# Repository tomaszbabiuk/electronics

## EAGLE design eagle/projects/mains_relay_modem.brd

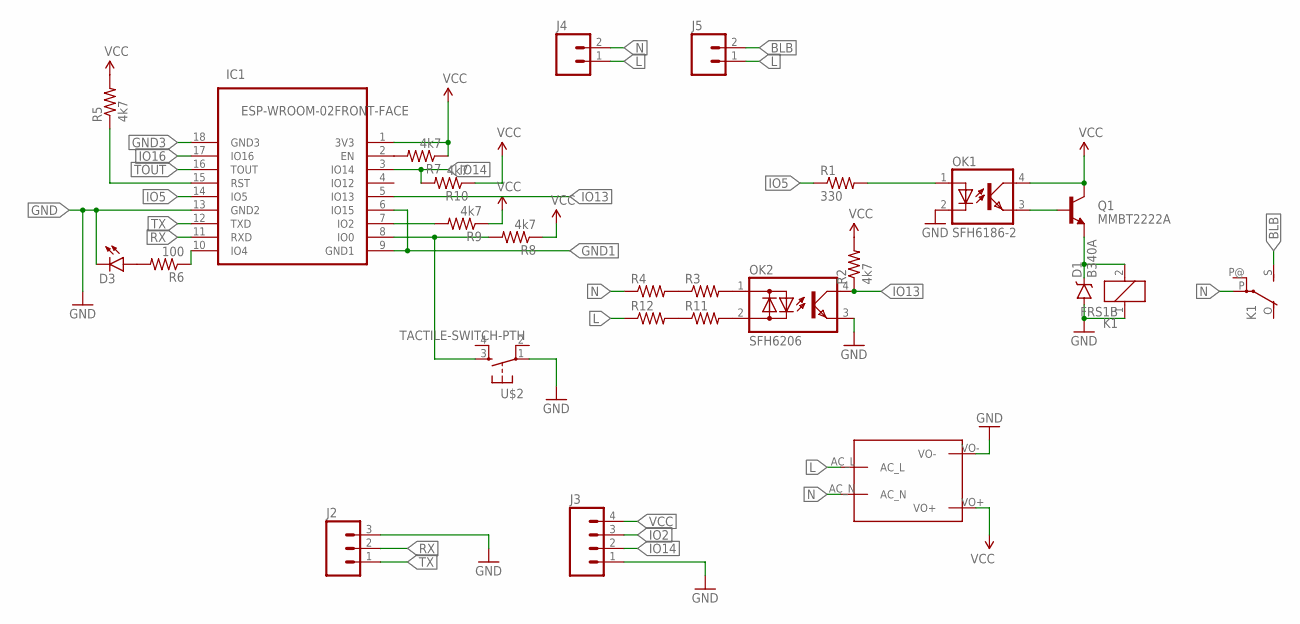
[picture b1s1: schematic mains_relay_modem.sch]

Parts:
D1: B340A; SMA-DIODE
D3: LED3MM
IC1: ESP-WROOM-02FRONT-FACE; FRONT-FACE
J2: M03PTH; 1X03
J3: M04NO_SILK_ALL_ROUND; 1X04_NO_SILK_ALL_ROUND
J4, J5: M025MM; SCREWTERMINAL-5MM-2
K1: FRS1B
OK1: SFH6186-2; SMD4
OK2: SFH6206; DIL4-SMD
Q1: MMBT2222A; SOT23-3
R1: 330; 0805
R2, R5, R7, R8, R9, R10: 4k7; 0805
R3, R4, R11, R12: RESISTOR0805-RES; 0805
R6: 100; 0805
U$1: MAINS_CONVERTERS; HLK-PM01
U$2: TACTILE-SWITCH-PTH; TAC-SWITCH-PTH

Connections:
BLB: J5.2, K1.S
GND: D1.A, D3.K (C), IC1.13 (GND2), J2.3, J3.1, K1.1, OK1.2 (C), OK2.3 (E), U$1.VO-, U$2.1
GND1: IC1.6 (IO15), IC1.9 (GND1)
GND3: IC1.18 (GND3)
IO2: IC1.7 (IO2), J3.3, R9.2
IO5: IC1.14 (IO5), R1.1
IO13: IC1.5 (IO13), OK2.4 (C), R2.1
IO14: IC1.3 (IO14), J3.2, R10.2
IO16: IC1.17 (IO16)
L: J4.1, J5.1, R12.1, U$1.AC_L
N: J4.2, K1.P, R4.1, U$1.AC_N
unnamed: IC1.10 (IO4), R6.1
unnamed: D3.A, R6.2
unnamed: IC1.2 (EN), R7.2
unnamed: D1.C, K1.2, Q1.2 (E)
unnamed: OK2.1 (AC1), R3.2
unnamed: R3.1, R4.2
unnamed: OK1.1 (A), R1.2
unnamed: OK1.3 (EMIT), Q1.1 (B)
unnamed: OK2.2 (AC2), R11.2
unnamed: IC1.15 (RST), R5.1
unnamed: IC1.8 (IO0), R8.2, U$2.3
unnamed: R11.1, R12.2
RX: IC1.11 (RXD), J2.2
TOUT: IC1.16 (TOUT)
TX: IC1.12 (TXD), J2.1
VCC: IC1.1 (3V3), J3.4, OK1.4 (COL), Q1.3 (C), R2.2, R5.2, R7.1, R8.1, R9.1, R10.1, U$1.VO+

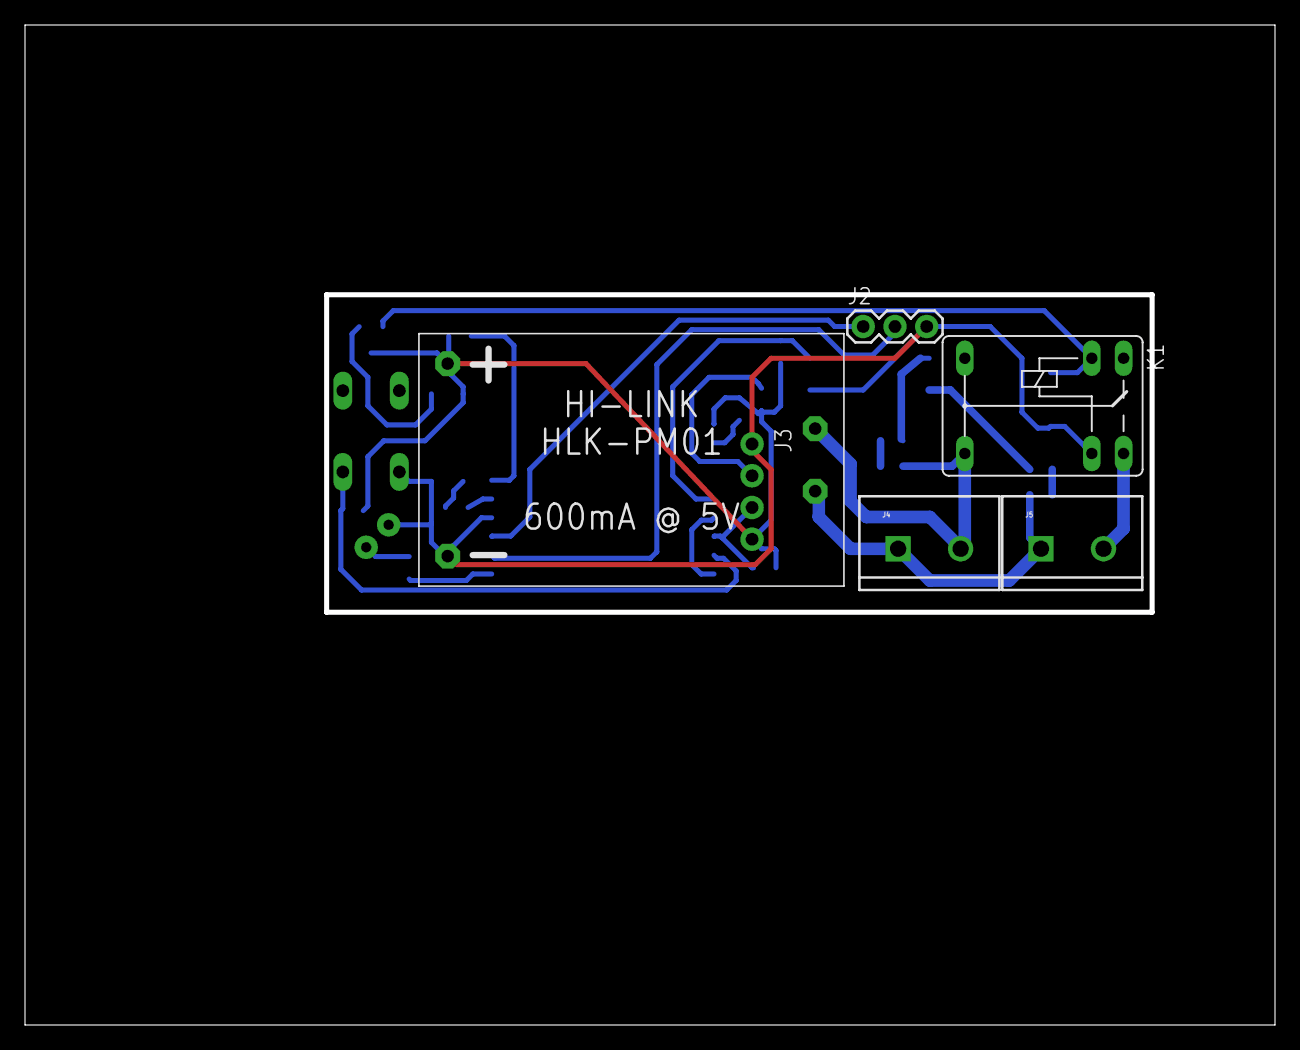
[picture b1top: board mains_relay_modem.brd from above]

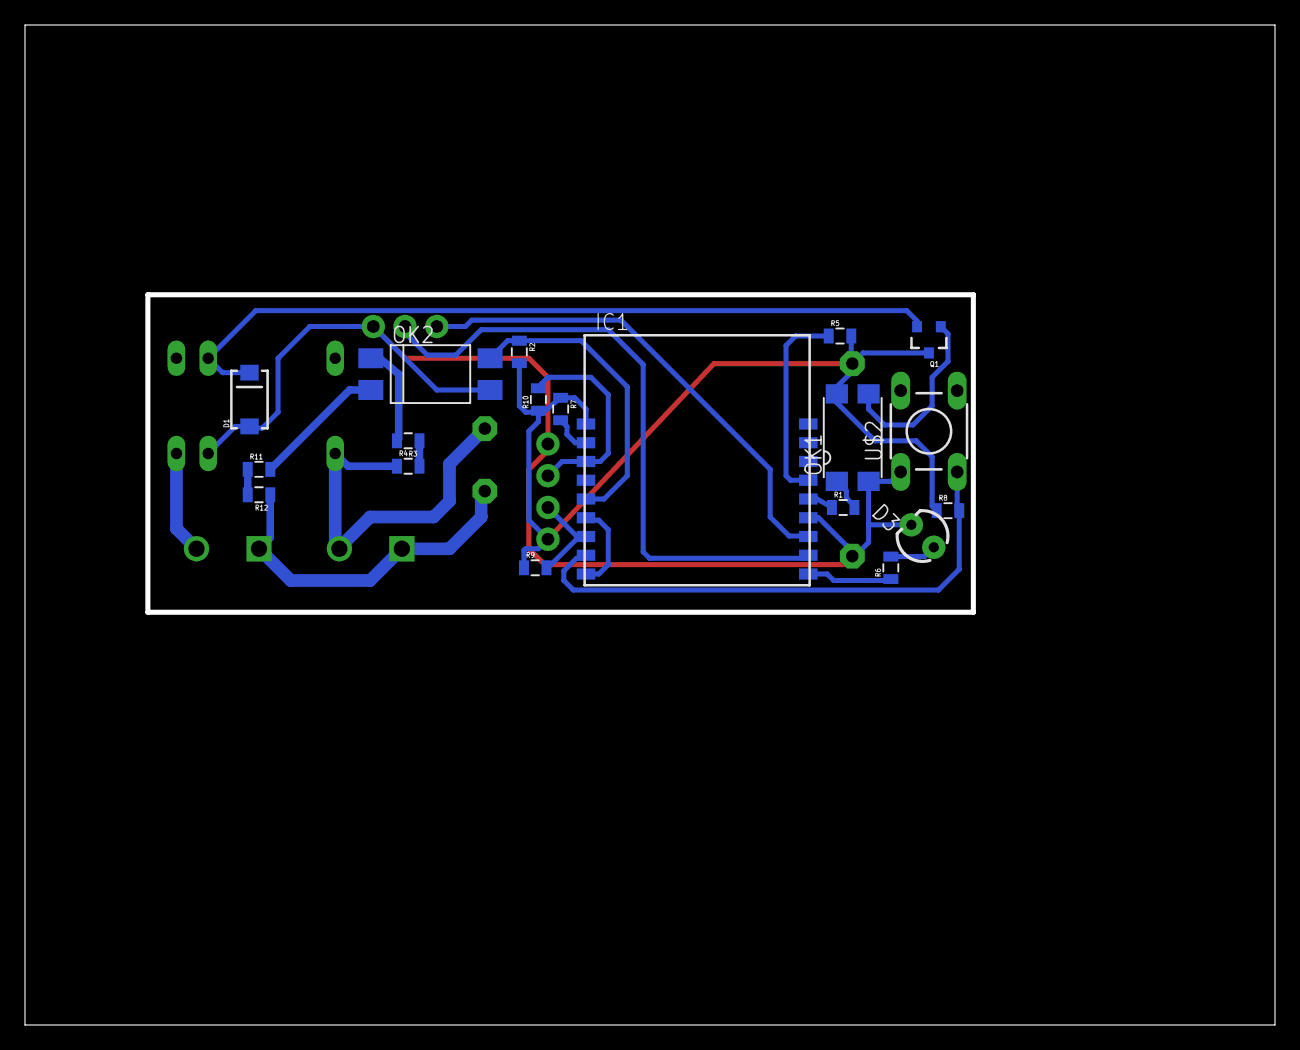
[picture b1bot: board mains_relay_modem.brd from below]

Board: 2 copper layers, 100.0 x 80.0 mm, 25 parts (19 on the bottom side), 24 nets.

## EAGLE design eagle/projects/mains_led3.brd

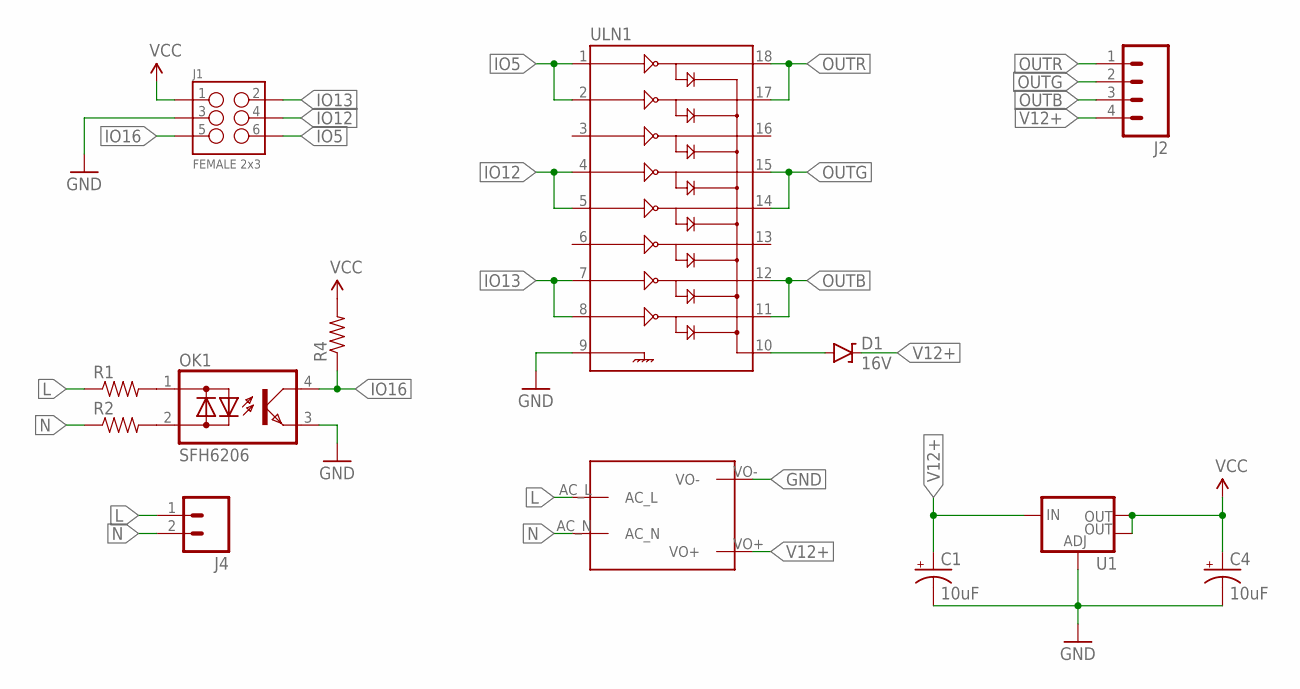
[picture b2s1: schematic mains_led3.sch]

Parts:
C1, C4: 10uF; EIA3216-KIT
D1: 16V; SOD-123
J1: FEMALE 2x3; 2X3-SHROUDED
J2: M04NO_SILK_ALL_ROUND; 1X04_NO_SILK_ALL_ROUND
J4: M023.5MM; SCREWTERMINAL-3.5MM-2
OK1: SFH6206; DIL4-SMD
R1, R2: RESISTORPTH-1/4W-VERT; AXIAL-0.1
R4: RESISTOR0805-RES; 0805
U1: V_REG_LM1117SOT223; SOT223
U$1: MAINS_CONVERTERS; HLK-PM01
ULN1: ULN2803SOICW; SO18L

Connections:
GND: C1.C (-), C4.C (-), J1.3, OK1.3 (E), U1.1 (ADJ), U$1.VO-, ULN1.9
IO5: J1.6, ULN1.1, ULN1.2
IO12: J1.4, ULN1.4, ULN1.5
IO13: J1.2, ULN1.7, ULN1.8
IO16: J1.5, OK1.4 (C), R4.1
L: J4.1, R1.P$1 (1), U$1.AC_L
N: J4.2, R2.P$1 (1), U$1.AC_N
unnamed: D1.A, ULN1.10
unnamed: OK1.1 (AC1), R1.P$2 (2)
unnamed: OK1.2 (AC2), R2.P$2 (2)
OUTB: J2.3, ULN1.11, ULN1.12
OUTG: J2.2, ULN1.14, ULN1.15
OUTR: J2.1, ULN1.17, ULN1.18
V12+: C1.A (+), D1.C, J2.4, U1.3 (IN), U$1.VO+
VCC: C4.A (+), J1.1, R4.2, U1.2 (OUT), U1.4 (OUT)

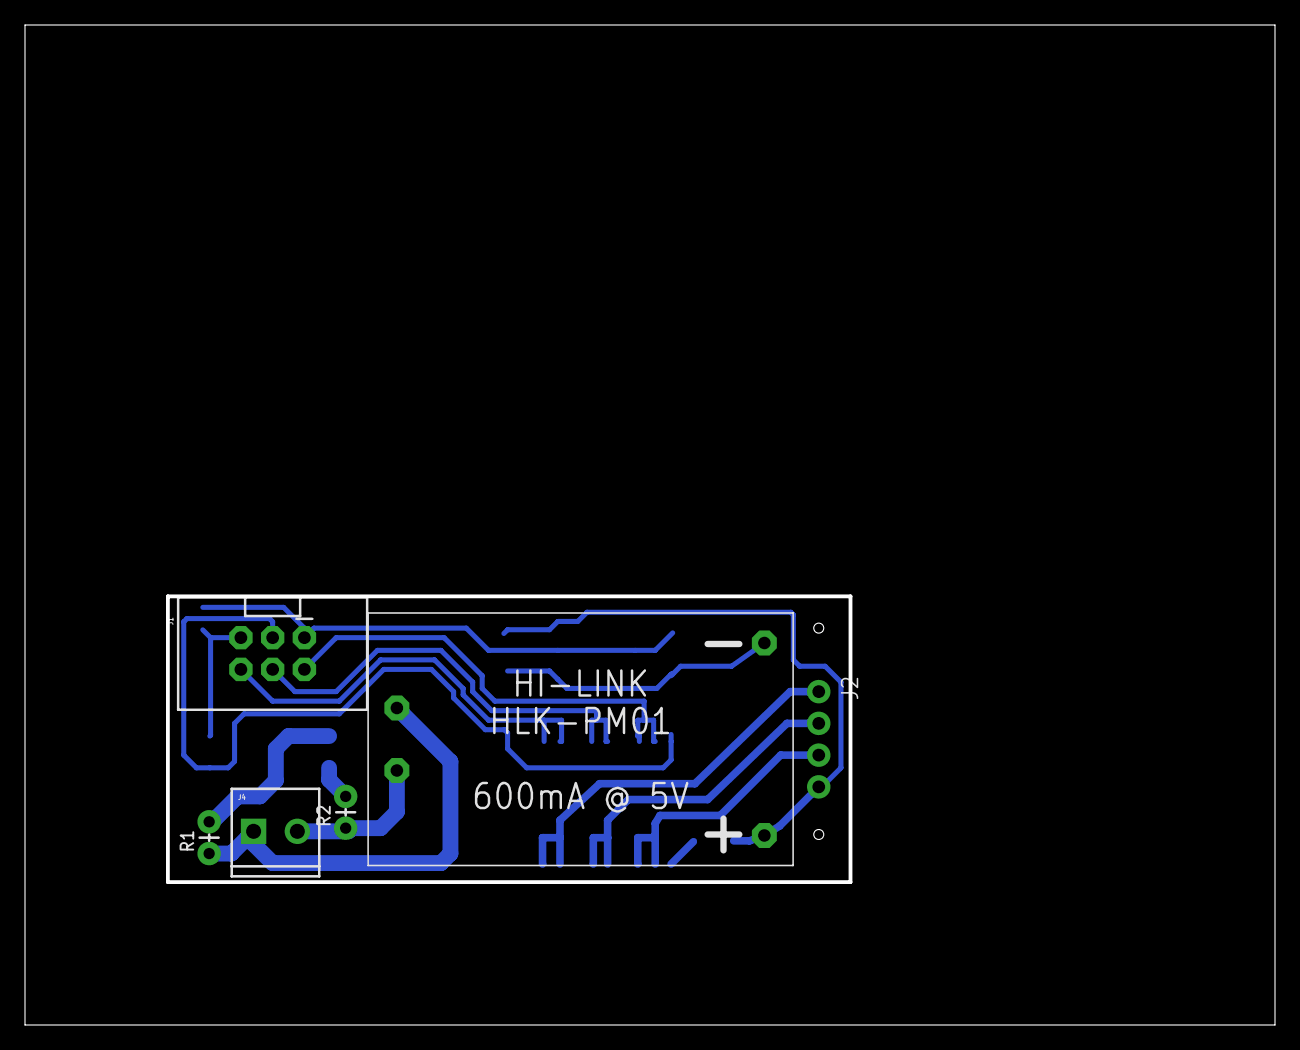
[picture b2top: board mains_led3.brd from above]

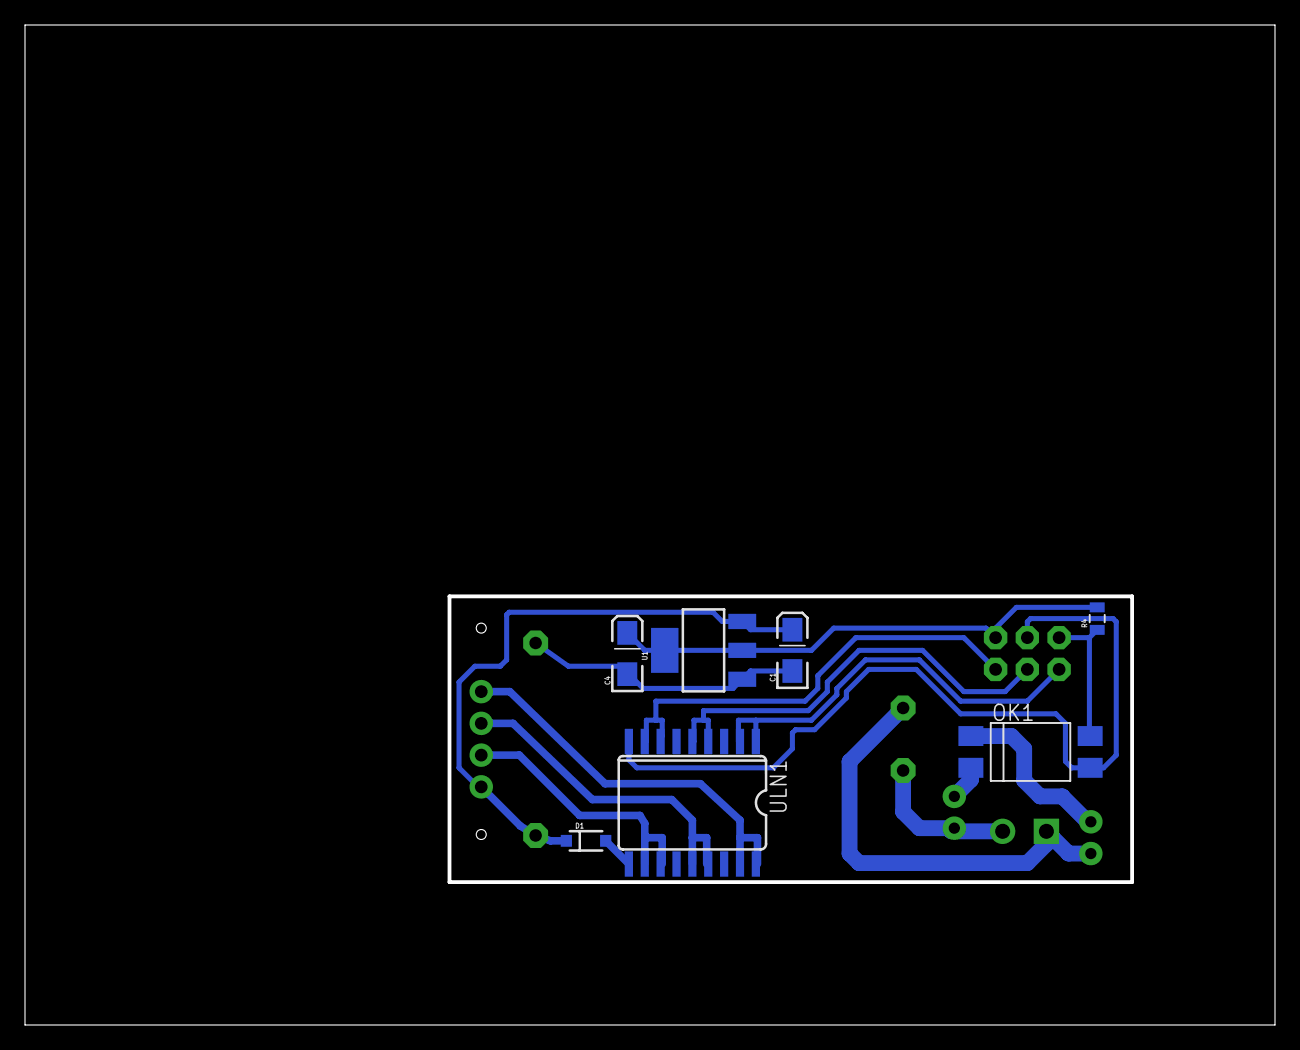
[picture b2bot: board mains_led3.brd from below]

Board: 2 copper layers, 100.0 x 80.0 mm, 13 parts (7 on the bottom side), 15 nets.

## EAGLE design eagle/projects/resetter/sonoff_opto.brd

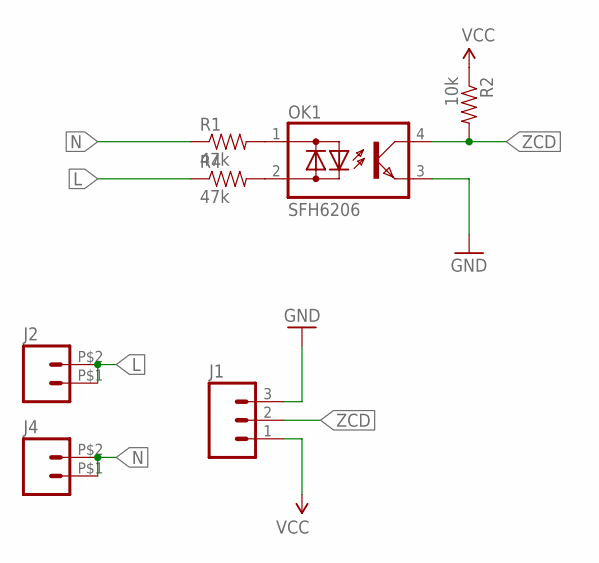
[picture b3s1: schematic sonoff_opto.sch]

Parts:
J1: M03PTH; 1X03
J2, J4: M02PTH2; 1X02_BIG
OK1: SFH6206; DIL4-SMD
R1, R4: 47k; AXIAL-0.4
R2: 10k; 0805

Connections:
GND: J1.3, OK1.3 (E)
L: J2.P$1 (1), J2.P$2 (2), R4.P$1 (1)
N: J4.P$1 (1), J4.P$2 (2), R1.P$1 (1)
unnamed: OK1.1 (AC1), R1.P$2 (2)
unnamed: OK1.2 (AC2), R4.P$2 (2)
VCC: J1.1, R2.1
ZCD: J1.2, OK1.4 (C), R2.2

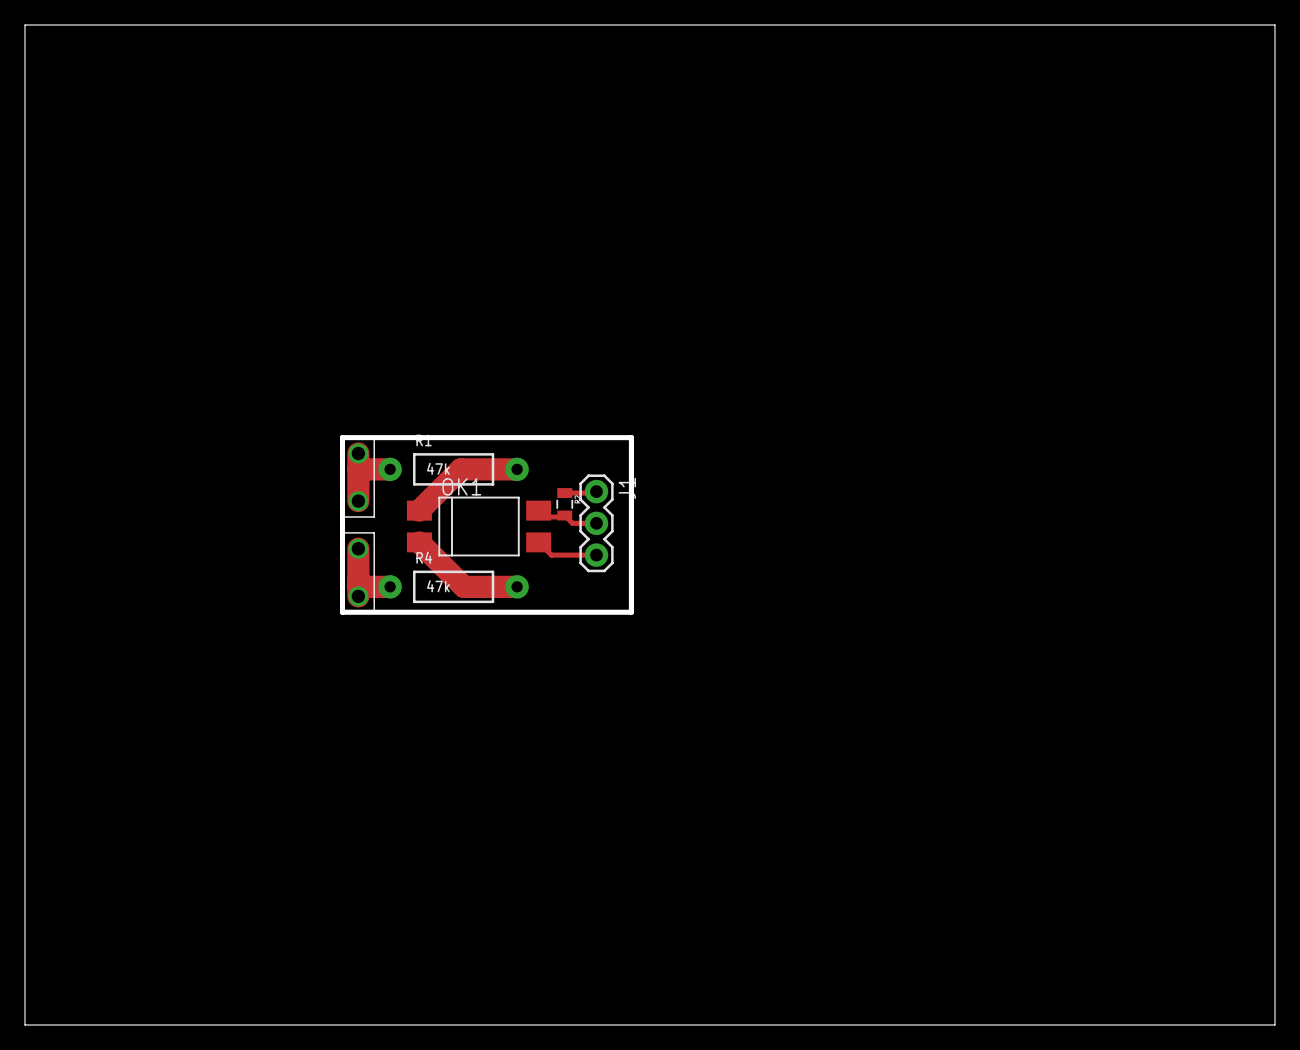
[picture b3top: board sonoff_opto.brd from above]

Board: 2 copper layers, 100.0 x 80.0 mm, 7 parts (0 on the bottom side), 7 nets.

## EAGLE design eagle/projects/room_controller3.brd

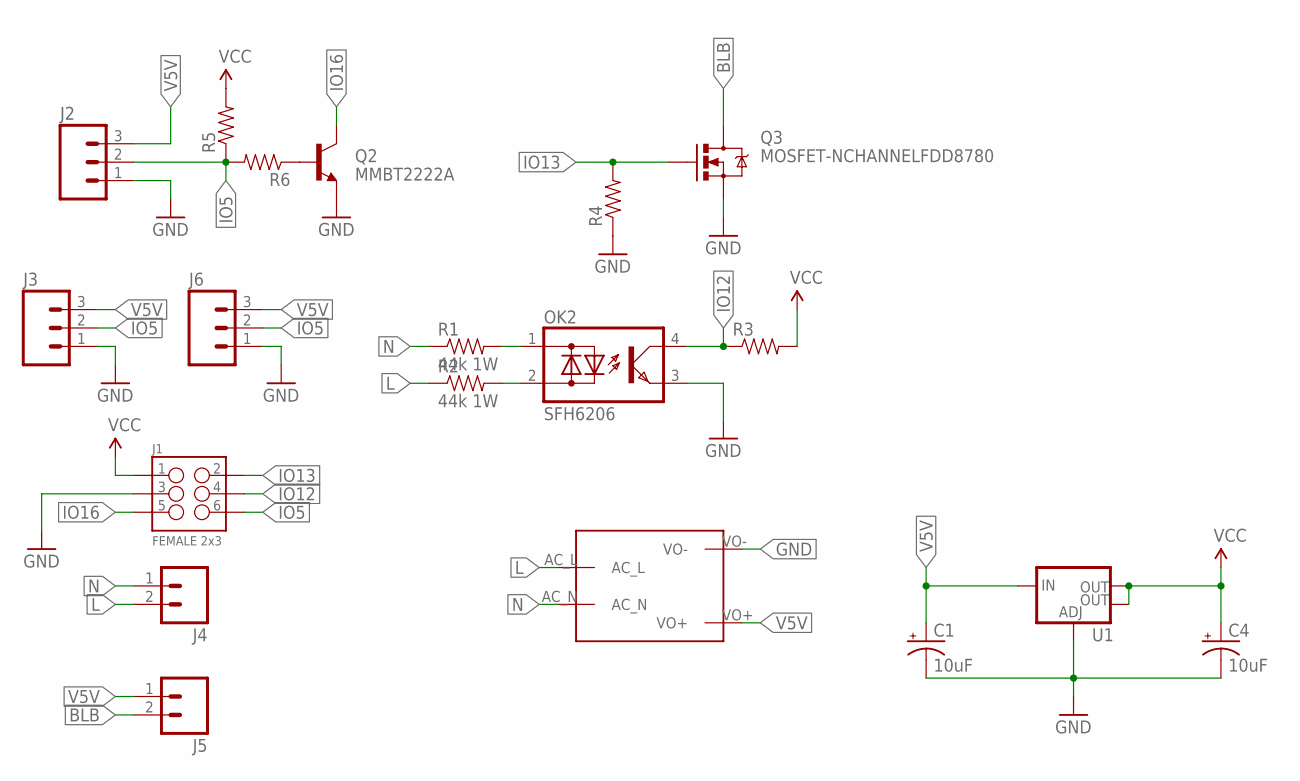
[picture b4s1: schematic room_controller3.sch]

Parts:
C1, C4: 10uF; EIA3216-KIT
J1: FEMALE 2x3; 2X3-SHROUDED
J2, J3, J6: M03PTH; 1X03
J4, J5: M025MM; SCREWTERMINAL-5MM-2
OK2: SFH6206; DIL4-SMD
Q2: MMBT2222A; SOT23-3
Q3: MOSFET-NCHANNELFDD8780; DPAK
R1, R2: 44k 1W; AXIAL-0.4
R3, R4, R5, R6: RESISTOR0805-RES; 0805
U1: V_REG_LM1117SOT223; SOT223
U$1: MAINS_CONVERTERS; HLK-PM01

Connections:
BLB: J5.2, Q3.4 (D)
GND: C1.C (-), C4.C (-), J1.3, J2.1, J3.1, J6.1, OK2.3 (E), Q2.2 (E), Q3.3 (S), R4.1, U1.1 (ADJ), U$1.VO-
IO5: J1.6, J2.2, J3.2, J6.2, R5.1, R6.2
IO12: J1.4, OK2.4 (C), R3.1
IO13: J1.2, Q3.1 (G), R4.2
IO16: J1.5, Q2.3 (C)
L: J4.2, R2.P$1 (1), U$1.AC_L
N: J4.1, R1.P$1 (1), U$1.AC_N
unnamed: OK2.1 (AC1), R1.P$2 (2)
unnamed: OK2.2 (AC2), R2.P$2 (2)
unnamed: Q2.1 (B), R6.1
V5V: C1.A (+), J2.3, J3.3, J5.1, J6.3, U1.3 (IN), U$1.VO+
VCC: C4.A (+), J1.1, R3.2, R5.2, U1.2 (OUT), U1.4 (OUT)

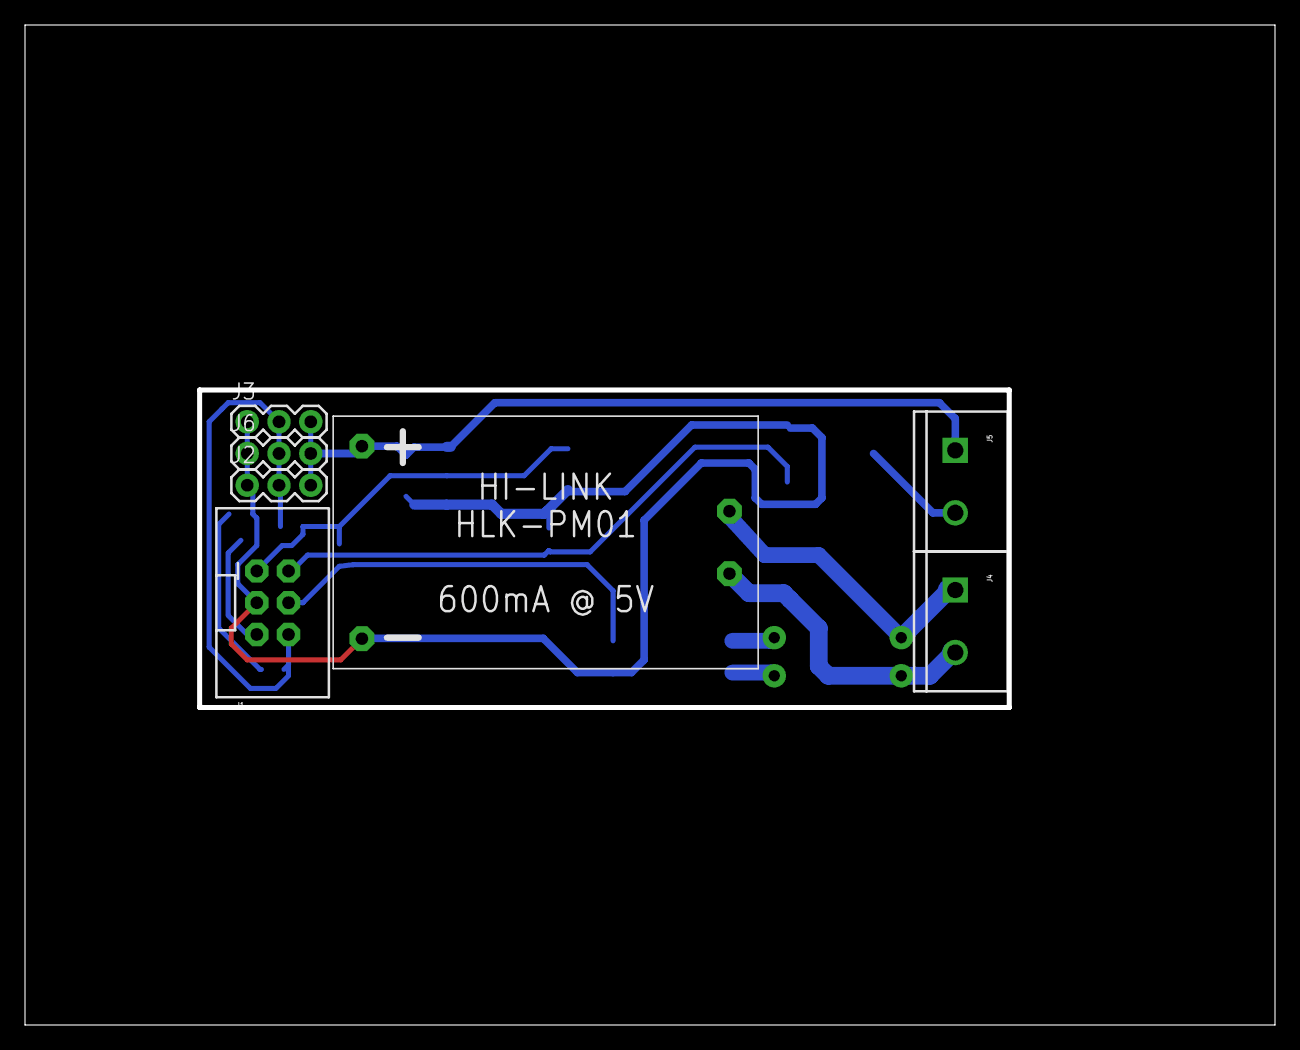
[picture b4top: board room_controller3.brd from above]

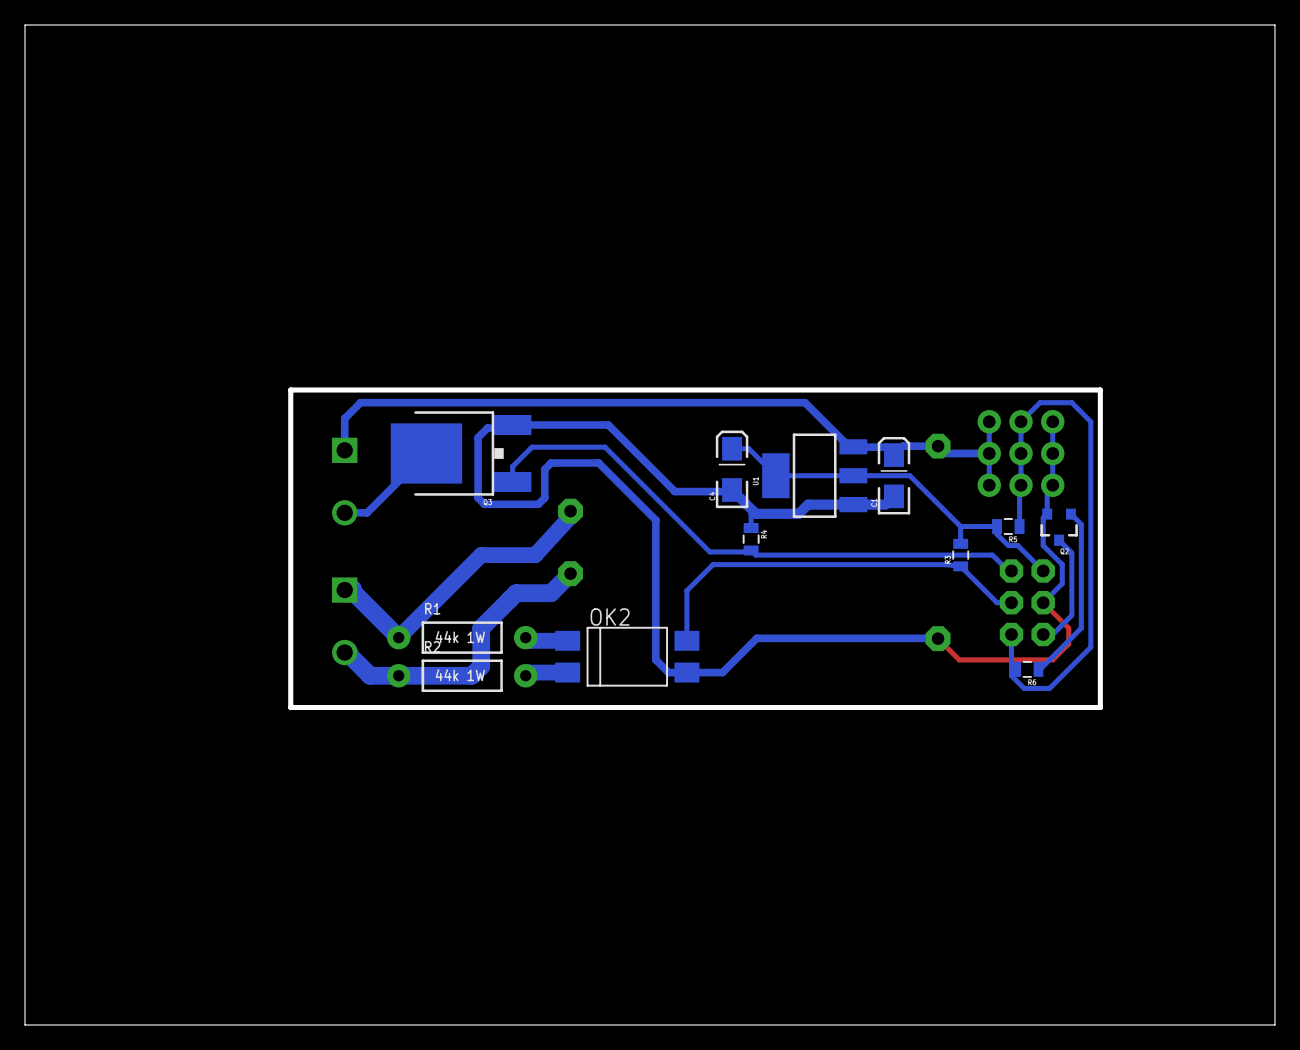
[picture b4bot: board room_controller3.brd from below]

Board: 2 copper layers, 100.0 x 80.0 mm, 19 parts (12 on the bottom side), 13 nets.

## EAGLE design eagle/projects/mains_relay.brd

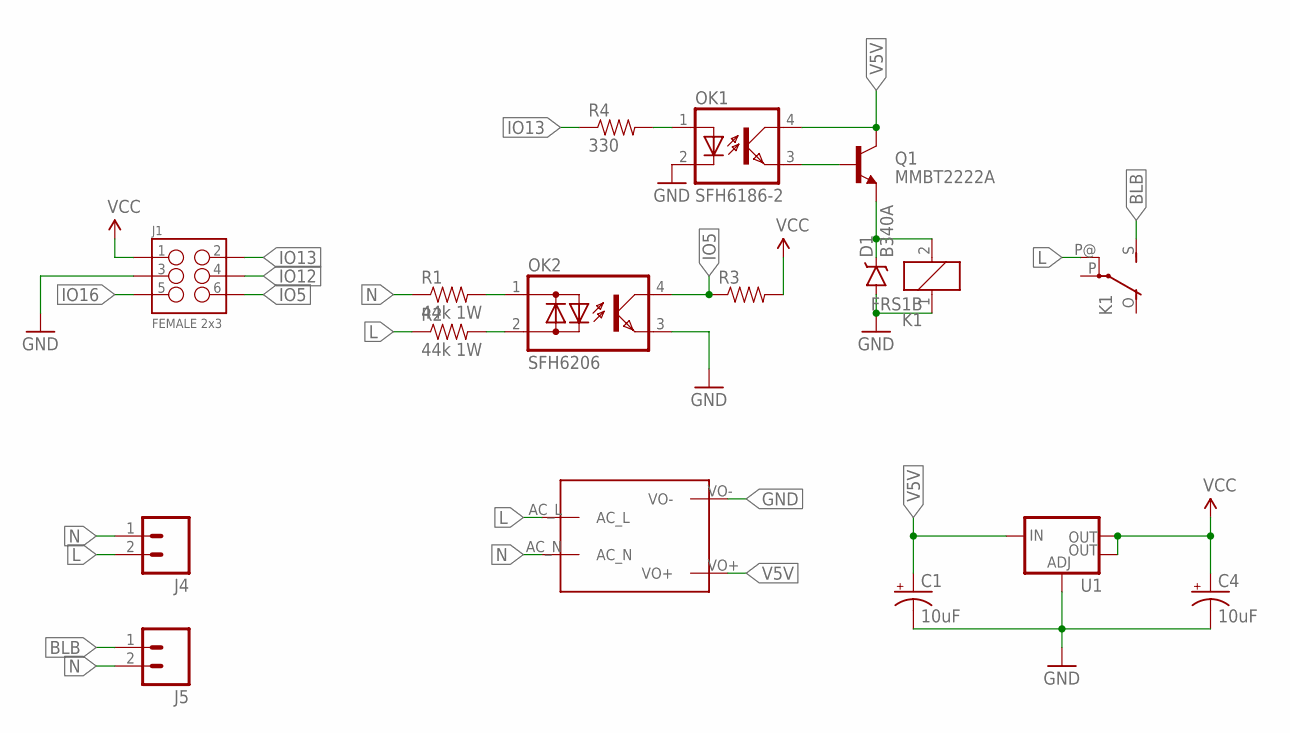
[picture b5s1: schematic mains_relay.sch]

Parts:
C1, C4: 10uF; EIA3216-KIT
D1: B340A; SMA-DIODE
J1: FEMALE 2x3; 2X3-SHROUDED
J4, J5: M025MM; SCREWTERMINAL-5MM-2
K1: FRS1B
OK1: SFH6186-2; SMD4
OK2: SFH6206; DIL4-SMD
Q1: MMBT2222A; SOT23-3
R1, R2: 44k 1W; AXIAL-0.4
R3: RESISTOR0805-RES; 0805
R4: 330; 0805
U1: V_REG_LM1117SOT223; SOT223
U$1: MAINS_CONVERTERS; HLK-PM01

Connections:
BLB: J5.1, K1.S
GND: C1.C (-), C4.C (-), D1.A, J1.3, K1.1, OK1.2 (C), OK2.3 (E), U1.1 (ADJ), U$1.VO-
IO5: J1.6, OK2.4 (C), R3.1
IO12: J1.4
IO13: J1.2, R4.1
IO16: J1.5
L: J4.2, K1.P@, R2.P$1 (1), U$1.AC_L
N: J4.1, J5.2, R1.P$1 (1), U$1.AC_N
unnamed: OK2.1 (AC1), R1.P$2 (2)
unnamed: OK2.2 (AC2), R2.P$2 (2)
unnamed: OK1.1 (A), R4.2
unnamed: D1.C, K1.2, Q1.2 (E)
unnamed: OK1.3 (EMIT), Q1.1 (B)
V5V: C1.A (+), OK1.4 (COL), Q1.3 (C), U1.3 (IN), U$1.VO+
VCC: C4.A (+), J1.1, R3.2, U1.2 (OUT), U1.4 (OUT)

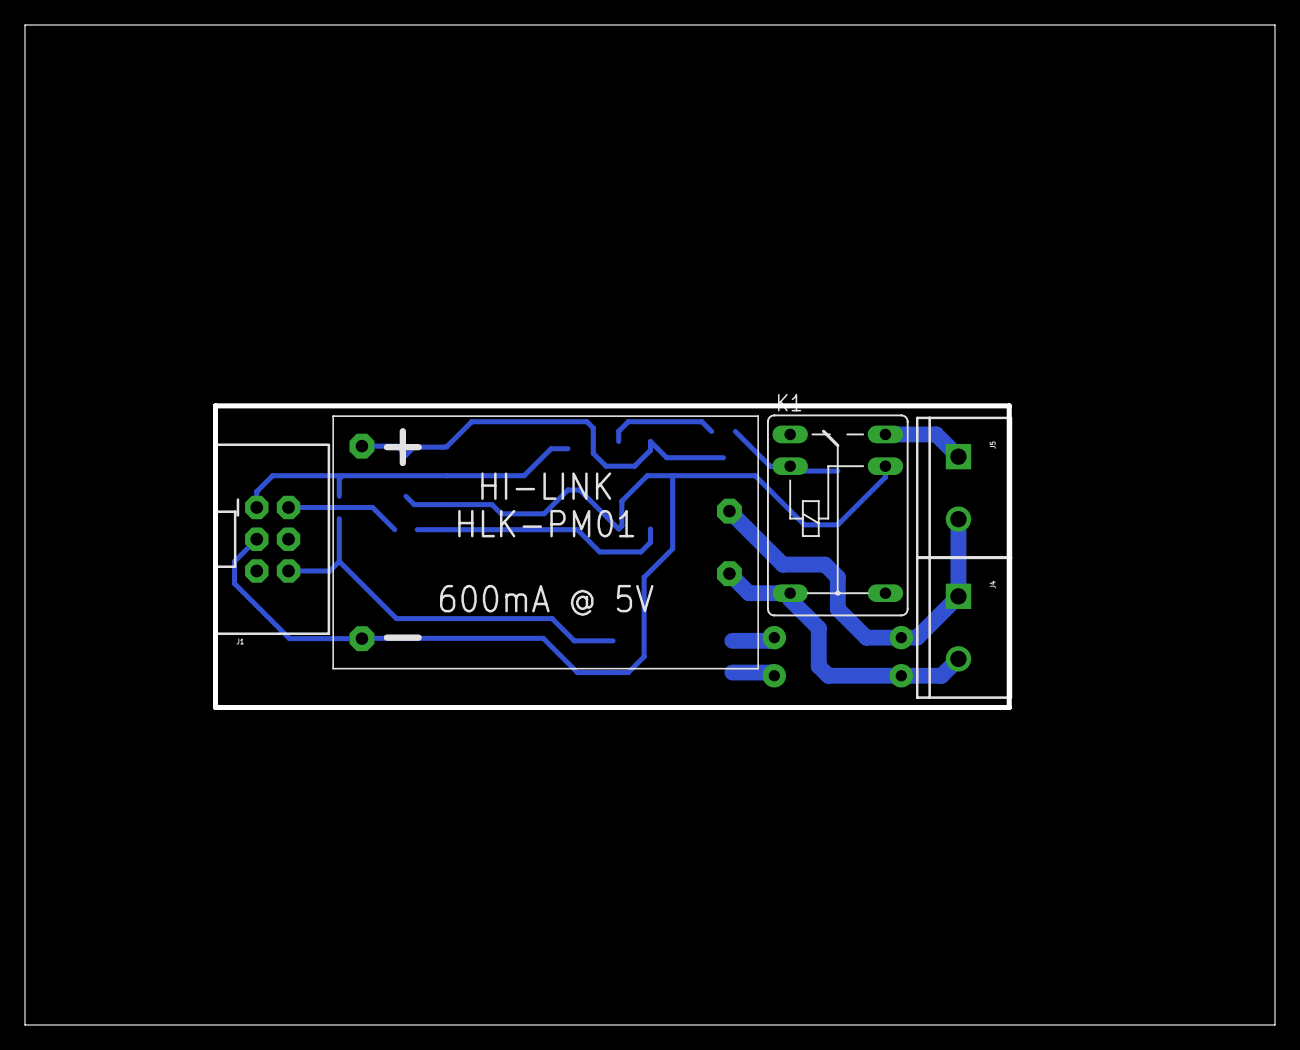
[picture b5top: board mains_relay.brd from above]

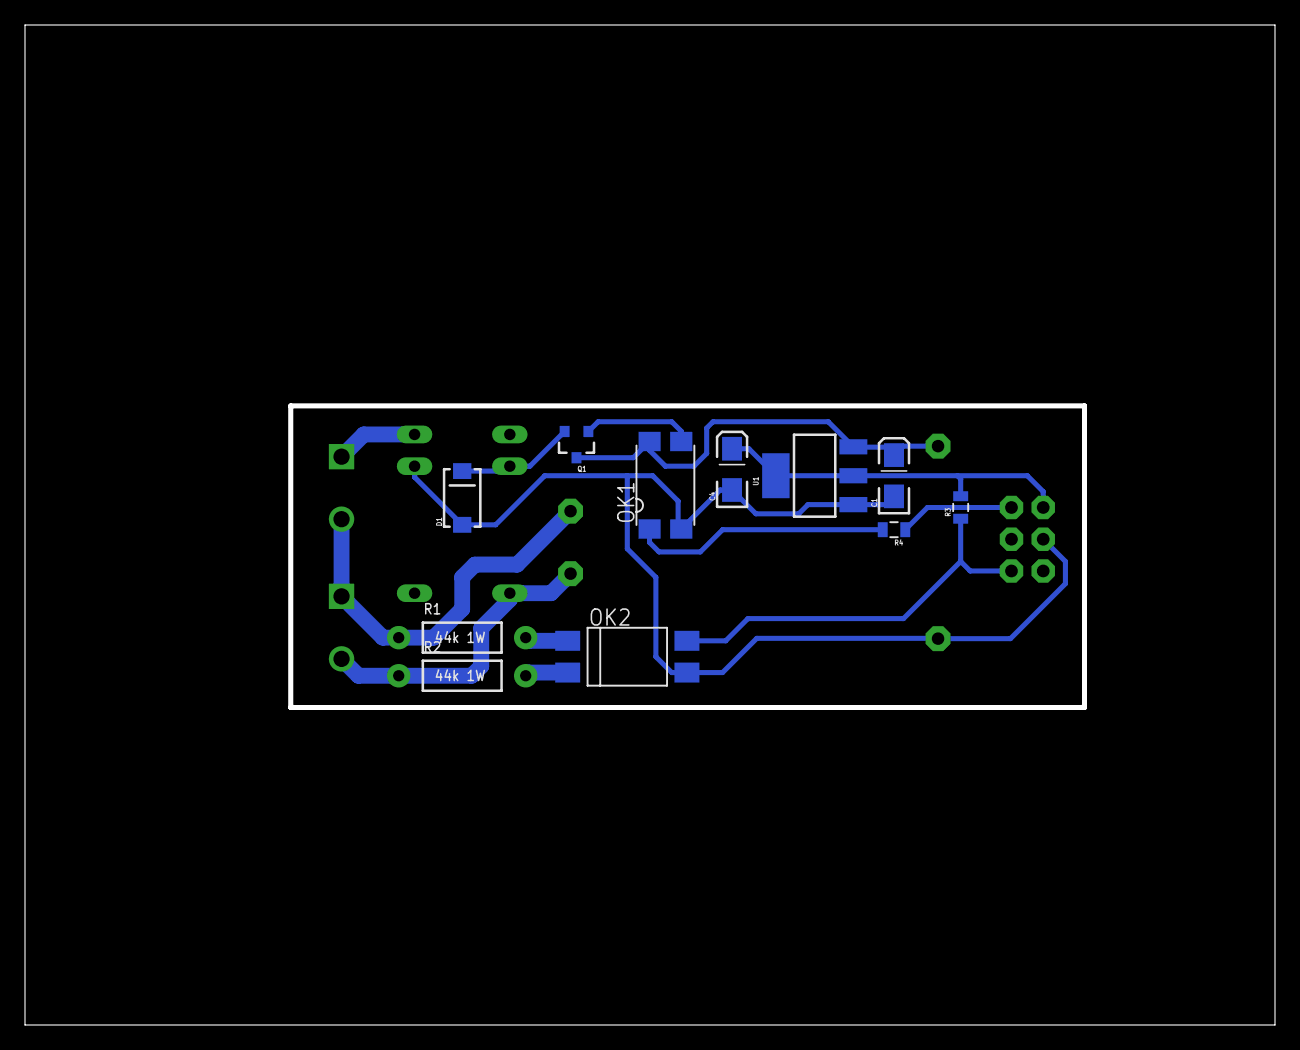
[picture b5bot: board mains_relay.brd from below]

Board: 2 copper layers, 100.0 x 80.0 mm, 16 parts (11 on the bottom side), 13 nets.

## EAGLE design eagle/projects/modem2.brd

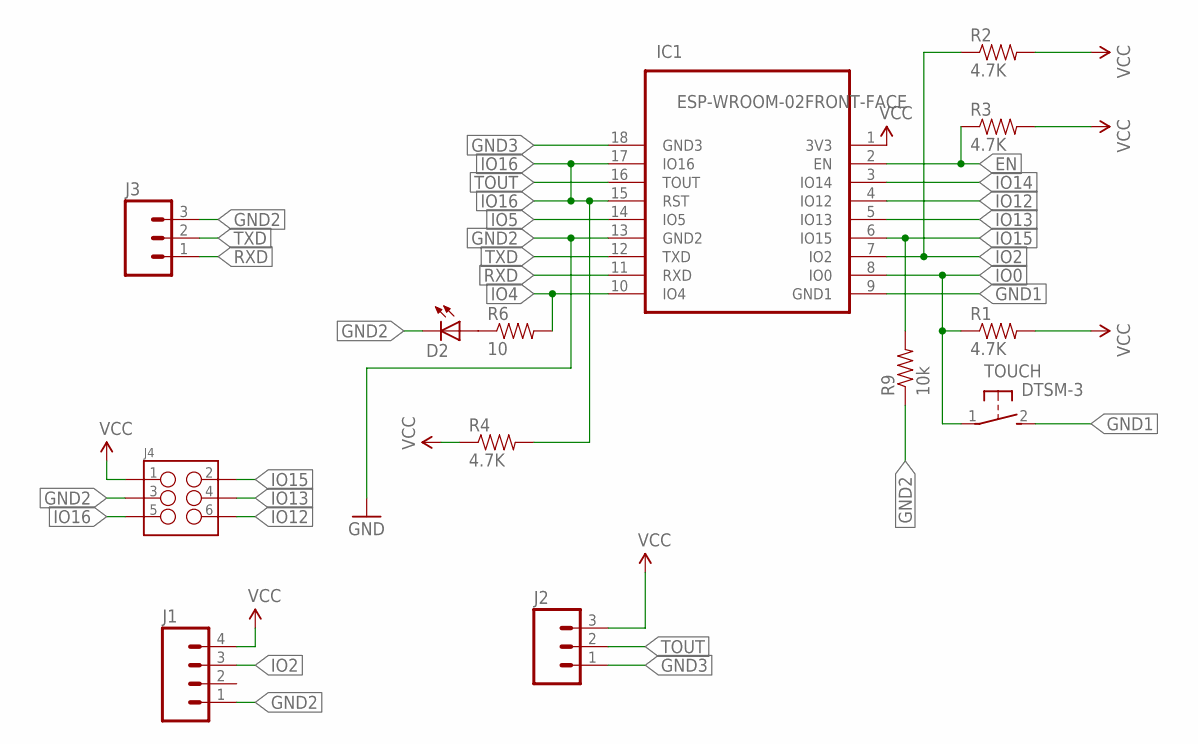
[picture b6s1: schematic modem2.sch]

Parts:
D2: LEDCHIPLED_0805; CHIPLED_0805
IC1: ESP-WROOM-02FRONT-FACE; FRONT-FACE
J1: M04NO_SILK_ALL_ROUND; 1X04_NO_SILK_ALL_ROUND
J2: M03PTH; 1X03
J3: M031X03_NO_SILK; 1X03_NO_SILK
J4: M03X2SHROUD; 2X3-SHROUDED
R1, R2, R3, R4: 4.7K; 0805
R6: 10; 0805
R9: 10k; 0805
TOUCH: DTSM-3

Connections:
EN: IC1.2 (EN), R3.1
GND1: IC1.9 (GND1), TOUCH.2
GND2: D2.C, IC1.13 (GND2), J1.1, J3.3, J4.3, R9.1
GND3: IC1.18 (GND3), J2.1
IO0: IC1.8 (IO0), R1.1, TOUCH.1
IO2: IC1.7 (IO2), J1.3, R2.1
IO4: IC1.10 (IO4), R6.2
IO5: IC1.14 (IO5)
IO12: IC1.4 (IO12), J4.6
IO13: IC1.5 (IO13), J4.4
IO14: IC1.3 (IO14)
IO15: IC1.6 (IO15), J4.2, R9.2
IO16: IC1.15 (RST), IC1.17 (IO16), J4.5, R4.2
unnamed: D2.A, R6.1
RXD: IC1.11 (RXD), J3.1
TOUT: IC1.16 (TOUT), J2.2
TXD: IC1.12 (TXD), J3.2
VCC: IC1.1 (3V3), J1.4, J2.3, J4.1, R1.2, R2.2, R3.2, R4.1

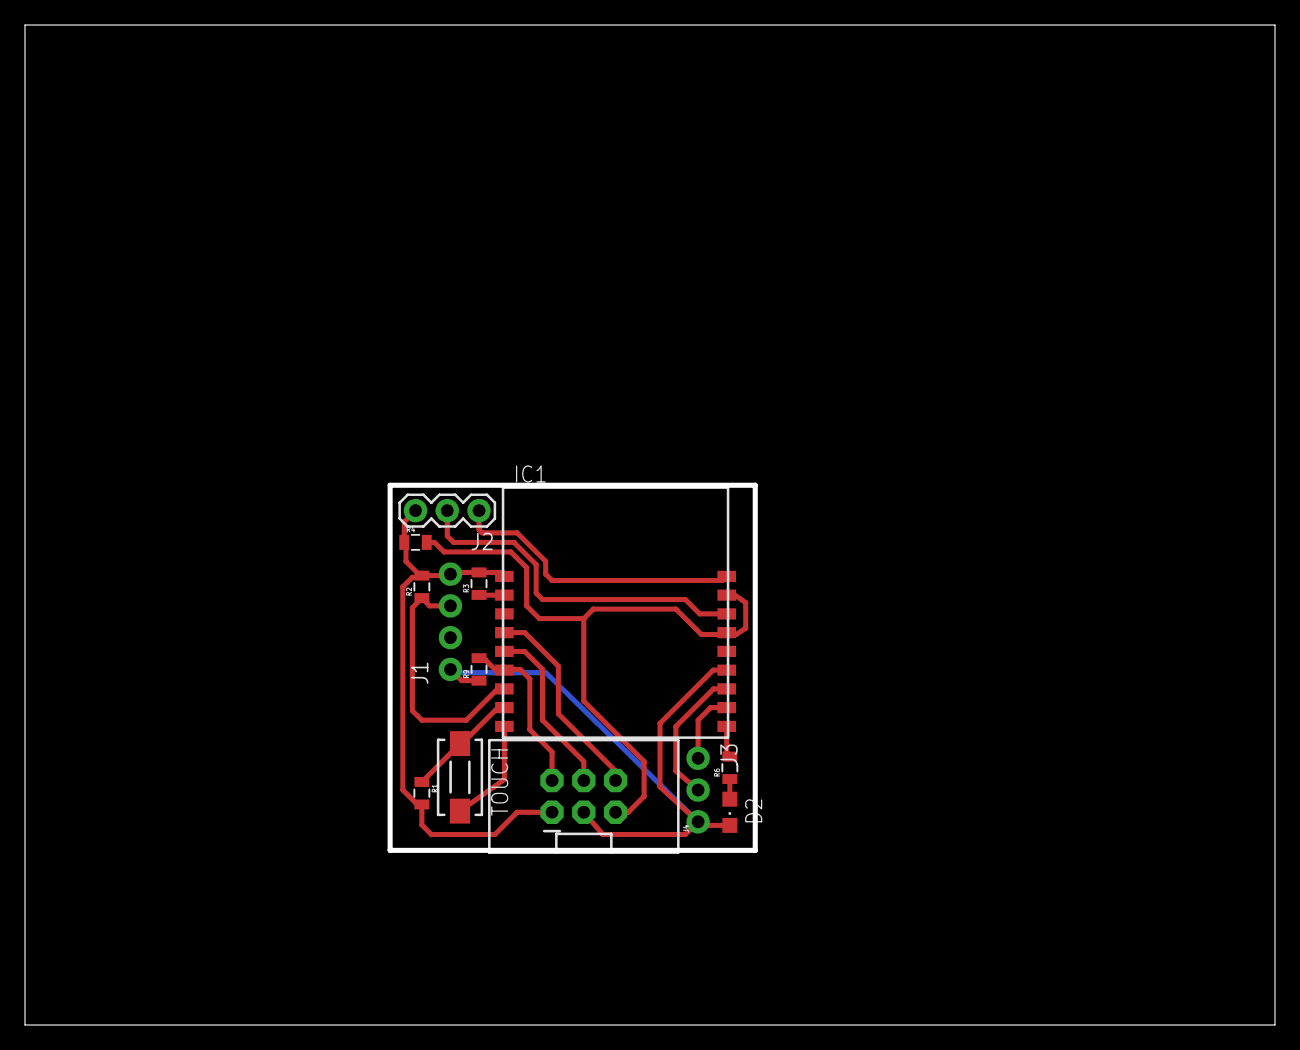
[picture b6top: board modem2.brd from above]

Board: 2 copper layers, 100.0 x 80.0 mm, 13 parts (0 on the bottom side), 16 nets.

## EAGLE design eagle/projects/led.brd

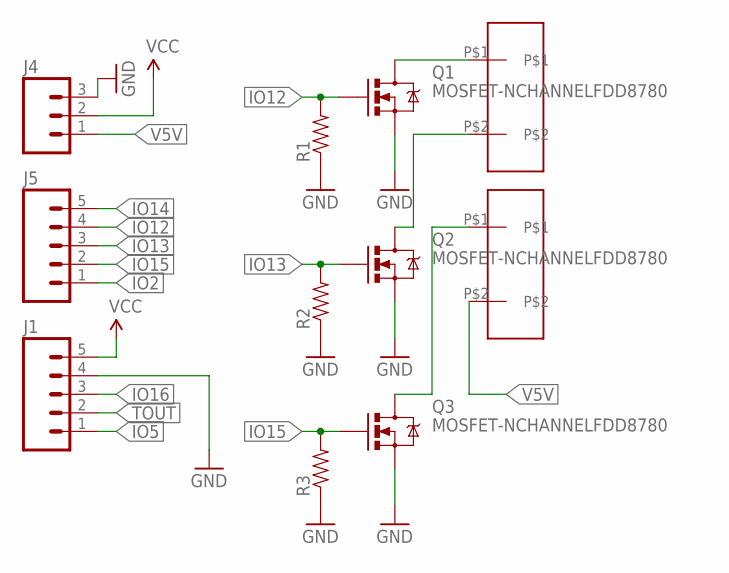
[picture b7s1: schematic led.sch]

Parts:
J1, J5: M05PTH; 1X05
J4: M03PTH; 1X03
Q1, Q2, Q3: MOSFET-NCHANNELFDD8780; DPAK
R1, R2, R3: RESISTOR0805-RES; 0805
U$1, U$2: SCREWTERMINALS_5MM_2; TERMINAL_2X

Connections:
GND: J1.4, J4.3, Q1.3 (S), Q2.3 (S), Q3.3 (S), R1.1, R2.1, R3.1
IO2: J5.1
IO5: J1.1
IO12: J5.4, Q1.1 (G), R1.2
IO13: J5.3, Q2.1 (G), R2.2
IO14: J5.5
IO15: J5.2, Q3.1 (G), R3.2
IO16: J1.3
unnamed: Q1.4 (D), U$1.P$1
unnamed: Q2.4 (D), U$1.P$2
unnamed: Q3.4 (D), U$2.P$1
TOUT: J1.2
V5V: J4.1, U$2.P$2
VCC: J1.5, J4.2

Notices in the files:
parts and their libraries:
SparkFun-Connectors: Licensing: Creative Commons ShareAlike 4.0 International - https://creativecommons.org/licenses/by-sa/4.0
